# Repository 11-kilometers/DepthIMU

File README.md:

The most important information needed for underwater navigation is how deep you are and what direction you're pointing. ROVs, AUVs, and even more passive marine systems need this information, so we've created a Depth/ IMU module for this purpose. The design is focused on robustness. It uses a Keller 7LD depth sensor which can be submerged for long periods of time, and a BNO 085 Inertial Measurment Unit (IMU) that has a 3-axis magnatometer, a 3-axis gyrometer, and a 3-axis magnitometer. The system uses the Bristlemouth underwater connectivity standard to communicate and get power, and the PCB has been designed to mate with a Bristlemouth Mote made by Sofar Ocean Technologies. The board is designed in KiCAD 8.0.4.

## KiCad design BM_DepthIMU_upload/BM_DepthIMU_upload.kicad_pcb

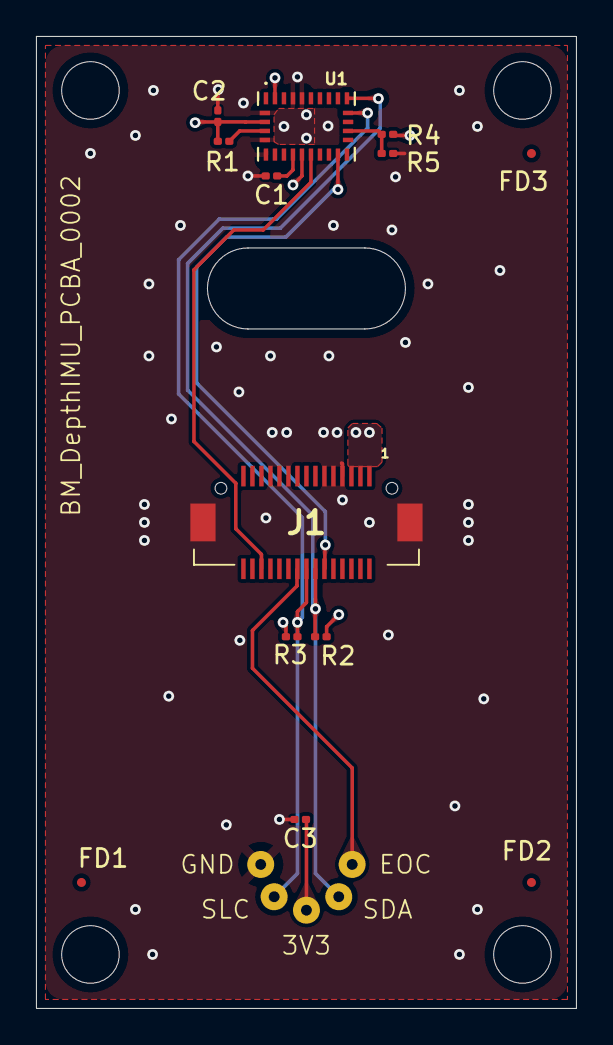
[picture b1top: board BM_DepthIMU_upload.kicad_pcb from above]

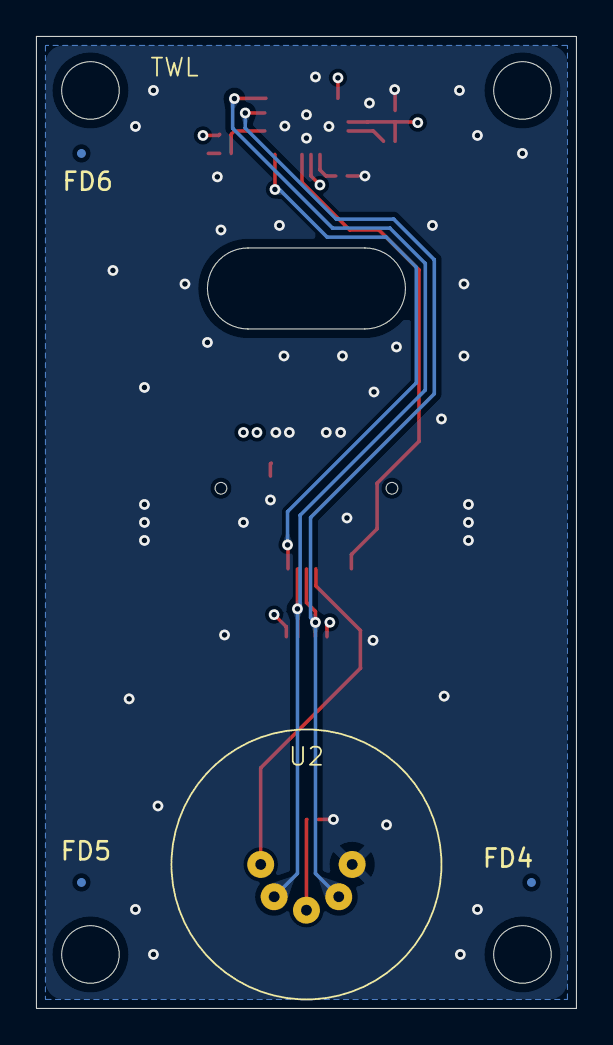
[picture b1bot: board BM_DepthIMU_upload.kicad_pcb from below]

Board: 4 copper layers, 30.0 x 54.0 mm, 17 parts (4 on the bottom side), 10 nets.

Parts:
C1, C2, C3: 100nF 16V X5R; C_0201_0603Metric
FD1, FD2, FD3, FD4, FD5, FD6: Fiducial_0.5mm_Mask1mm
J1: DF17_2.0_-30DP-0.5V_57_; DF172030DP05V57
R1: 10K; R_0201_0603Metric
R2, R3: 2K2; R_0201_0603Metric
R4: 0; R_0201_0603Metric
R5: 0R; R_0201_0603Metric
U1: BNO085; IC_BNO085
U2: Series 7LD; PA-7LD

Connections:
+3.3V: C2.1, C3.1, J1.1, J1.3, J1.5, R1.1, R2.1, R3.1, R4.1, U1.3 (VDD), U1.10 (CLKSEL0), U1.28 (VDDIO), U2.3 (SUP)
EOC: J1.18, U2.1 (EOC)
GND: C1.2, C2.2, C3.2, J1.7, J1.9, J1.11, J1.19, J1.21, J1.23, J1.MP1, J1.MP2, R5.2, U1.2 (GND), U1.5 (PS1), U1.6 (PS0/WAKE), U1.25 (GNDIO), U1.26 (XOUT32/CLKSEL1), U2.5 (GND)
unnamed: C1.1, U1.9 (CAP)
unnamed: R4.2, R5.1, U1.17 (SA0/H_MOSI)
unnamed: R1.2, U1.4 (~BOOT)
SDA: J1.14, R2.2, U1.20 (H_SDA/H_MISO/TX), U2.2 (SDA)
SLC: J1.16, R3.2, U1.19 (H_SCL/SCK/RX), U2.4 (SCL)
~IMU_INT: J1.12, U1.14 (~H_INT)
~IMU_RST: J1.26, U1.11 (~RST)

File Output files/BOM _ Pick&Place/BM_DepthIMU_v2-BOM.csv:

Comment,Designator,Footprint,JLCPCB Part #
100nF 16V X5R,"C1,C2,C3",Capacitor_SMD:C_0201_0603Metric,C5677646
DF17(2.0)-30DP-0.5V(57),J1,Hirose Connectors:DF172030DP05V57,
10K 25V 50mW,R1,Resistor_SMD:R_0201_0603Metric,C253350
2K2 25V 50mW,"R2,R3",Resistor_SMD:R_0201_0603Metric,C239976
0R 25V 50mW,R5,Resistor_SMD:R_0201_0603Metric,C170193
BNO085,U1,Sensor Motion BNO085:IC_BNO085,C5189642

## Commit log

2025-02-25 Create README.md
    Initial description done on the fly- improvements to come!
2025-02-25 Add files via upload
    KiCAD Schematic and Layout files for the DepthIMU PCB.
2025-02-25 Add files via upload
    DepthIMU PCBA BOM, pick & place, gerber & drill files.
2025-03-05 Add files via upload
    PDF Schematic of the BM DepthIMU PCB
